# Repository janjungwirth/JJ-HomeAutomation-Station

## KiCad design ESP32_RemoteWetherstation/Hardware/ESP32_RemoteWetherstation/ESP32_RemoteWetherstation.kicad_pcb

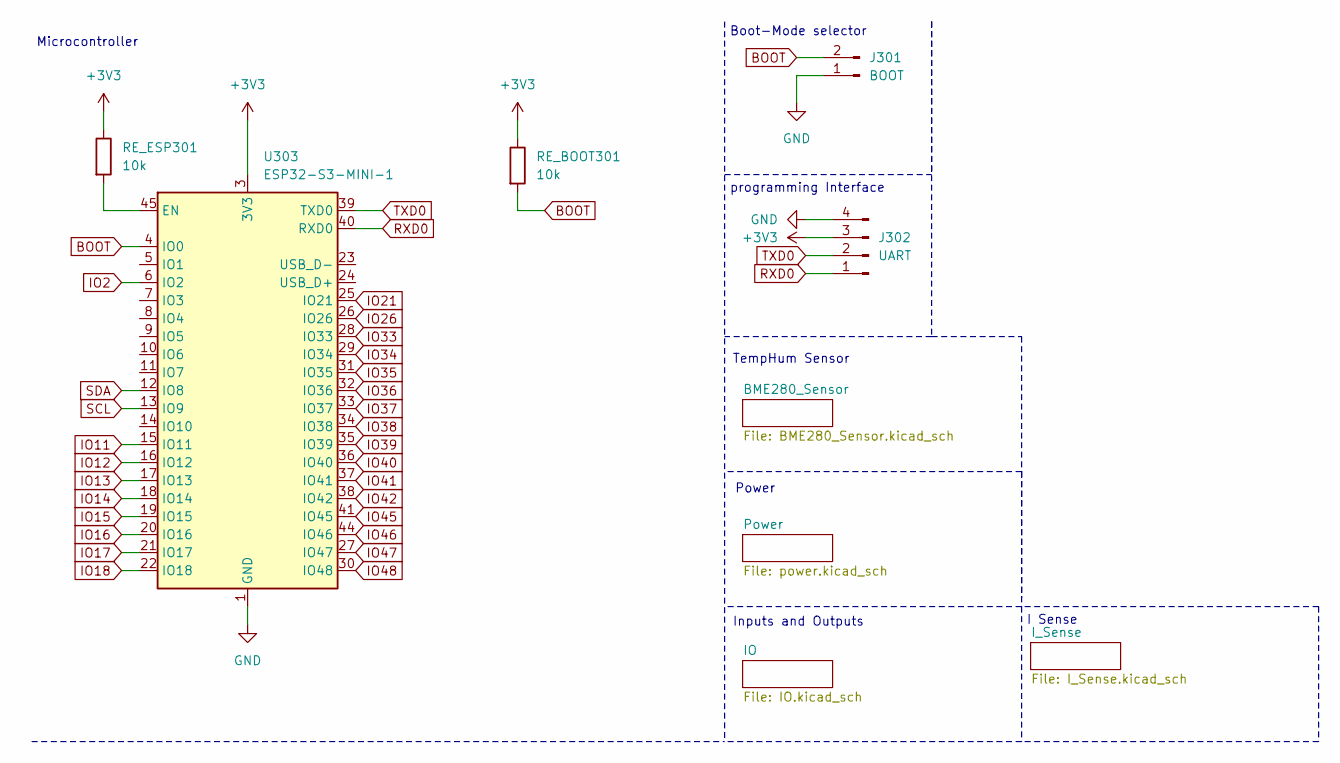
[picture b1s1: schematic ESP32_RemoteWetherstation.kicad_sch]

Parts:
J301: BOOT; PinHeader_1x02_P2.00mm_Vertical
J302: UART; PinHeader_1x04_P2.54mm_Vertical
RE_BOOT301: 10k; R_0402_1005Metric
RE_ESP301: 10k; R_0402_1005Metric
U303: ESP32-S3-MINI-1; ESP32-S2-MINI-1

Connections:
+3V3: J302.3, RE_BOOT301.1, RE_ESP301.1, U303.3 (3V3); also elsewhere on the board
BOOT: J301.2, RE_BOOT301.2, U303.4 (IO0)
GND: J301.1, J302.4, U303.1 (GND), U303.2 (GND), U303.42 (GND), U303.43 (GND), U303.46 (GND), U303.47 (GND), U303.48 (GND), U303.49 (GND), U303.50 (GND), U303.51 (GND), U303.52 (GND), U303.53 (GND), U303.54 (GND), U303.55 (GND), U303.56 (GND), U303.57 (GND), U303.58 (GND), U303.59 (GND), U303.60 (GND), U303.61 (GND), U303.62 (GND), U303.63 (GND), U303.64 (GND), U303.65 (GND); also elsewhere on the board
IO2: U303.6 (IO2)
IO11: U303.15 (IO11)
IO12: U303.16 (IO12); also elsewhere on the board
IO13: U303.17 (IO13); also elsewhere on the board
IO14: U303.18 (IO14); also elsewhere on the board
IO15: U303.19 (IO15)
IO16: U303.20 (IO16)
IO17: U303.21 (IO17)
IO18: U303.22 (IO18); also elsewhere on the board
IO21: U303.25 (IO21)
IO26: U303.26 (IO26)
IO33: U303.28 (IO33); also elsewhere on the board
IO34: U303.29 (IO34); also elsewhere on the board
IO35: U303.31 (IO35)
IO36: U303.32 (IO36)
IO37: U303.33 (IO37)
IO38: U303.34 (IO38)
IO39: U303.35 (IO39)
IO40: U303.36 (IO40)
IO41: U303.37 (IO41)
IO42: U303.38 (IO42)
IO45: U303.41 (IO45)
IO46: U303.44 (IO46)
IO47: U303.27 (IO47); also elsewhere on the board
IO48: U303.30 (IO48); also elsewhere on the board
unnamed: RE_ESP301.2, U303.45 (EN)
RXD0: J302.1, U303.40 (RXD0)
SCL: U303.13 (IO9); also elsewhere on the board
SDA: U303.12 (IO8); also elsewhere on the board
TXD0: J302.2, U303.39 (TXD0)

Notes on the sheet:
Power
Inputs and Outputs
programming Interface
I Sense
Microcontroller
Boot-Mode selector
TempHum Sensor

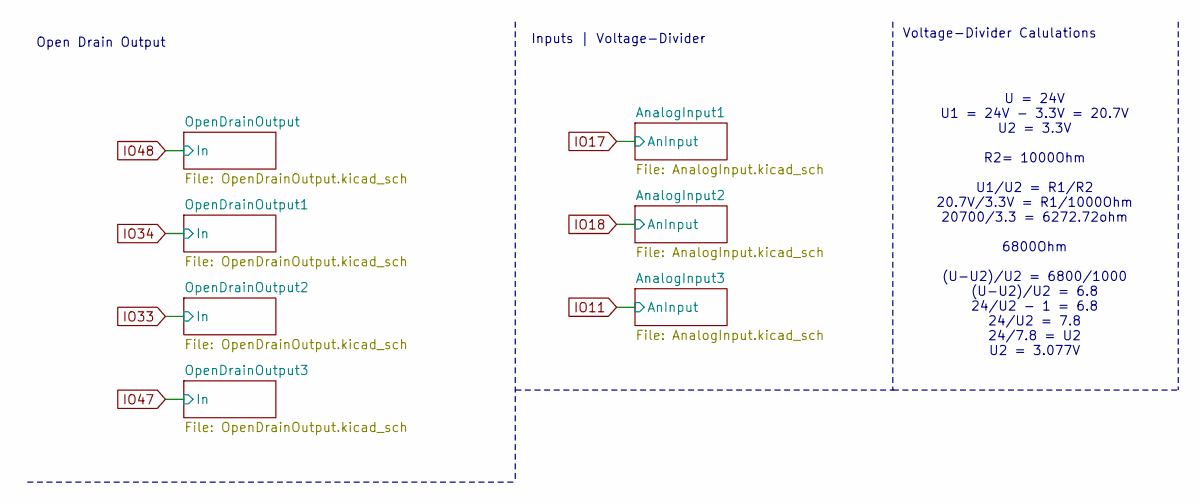
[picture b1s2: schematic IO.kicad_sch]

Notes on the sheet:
Voltage-Divider Calulations
Open Drain Output
U = 24V U1 = 24V - 3.3V = 20.7V U2 = 3.3V R2= 1000Ohm U1/U2 = R1/R2 20.7V/3.3V = R1/1000Ohm 20700/3.3 = 6272.72ohm 6800Ohm (U-U2)/U2 = 6800/1000 (U-U2)/U2 = 6.8 24/U2 - 1 = 6.8 24/U2 = 7.8 24/7.8 = U2 U2 = 3.077V
Inputs | Voltage-Divider

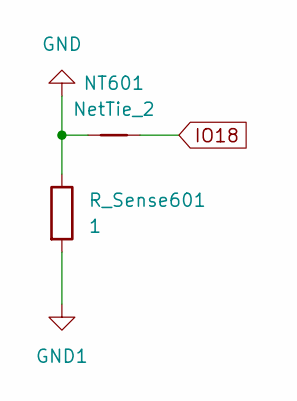
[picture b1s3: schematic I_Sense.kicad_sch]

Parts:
NT601: NetTie_2; NetTie-2_SMD_Pad0.5mm
R_Sense601: 1; R_0805_2012Metric

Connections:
GND: NT601.1, R_Sense601.1; also elsewhere on the board
GND1: R_Sense601.2; also elsewhere on the board
IO18: NT601.2; also elsewhere on the board

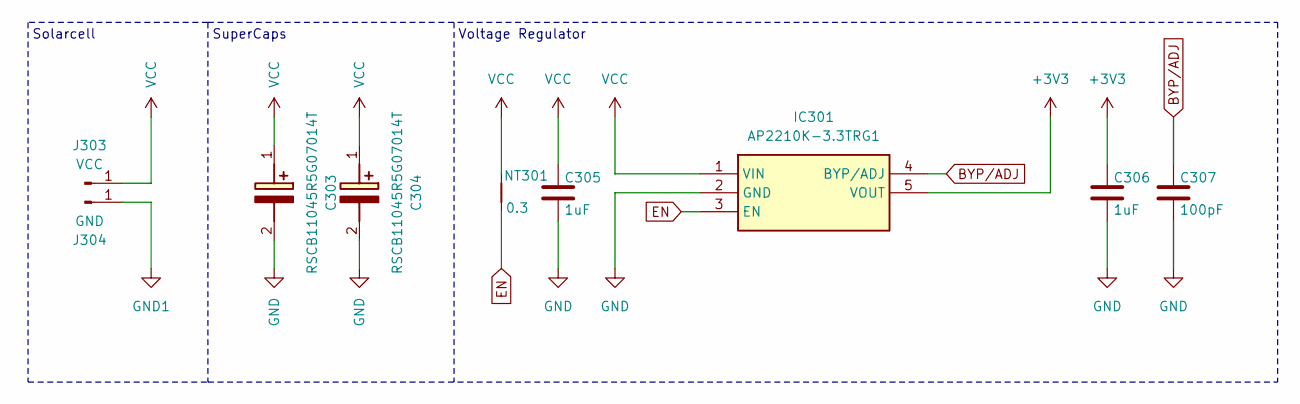
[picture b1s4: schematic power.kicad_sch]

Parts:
C303, C304: RSCB11045R5G07014T; Manufacturer_Part_Number RSCB11045R5G07014T
C305, C306: 1uF; C_0805_2012Metric_Pad1.18x1.45mm_HandSolder
C307: 100pF; C_0402_1005Metric
IC301: AP2210K-3.3TRG1; SOT95P282X145-5N; Mouser Part Number 621-AP2210K-3.3TRG1
J303: VCC; SolderWire-0.75sqmm_1x01_D1.25mm_OD2.3mm
J304: GND; SolderWire-0.75sqmm_1x01_D1.25mm_OD2.3mm
NT301: 0.3; NetTie-2_SMD_Pad0.3mm

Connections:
+3V3: C306.1, IC301.5 (VOUT); also elsewhere on the board
BYP/ADJ: C307.1, IC301.4 (BYP/ADJ)
EN: IC301.3 (EN), NT301.1
GND: C303.2 (-), C304.2 (-), C305.2, C306.2, C307.2, IC301.2 (GND); also elsewhere on the board
GND1: J304.1; also elsewhere on the board
VCC: C303.1 (+), C304.1 (+), C305.1, IC301.1 (VIN), J303.1, NT301.2

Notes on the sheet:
SuperCaps
Voltage Regulator
Solarcell

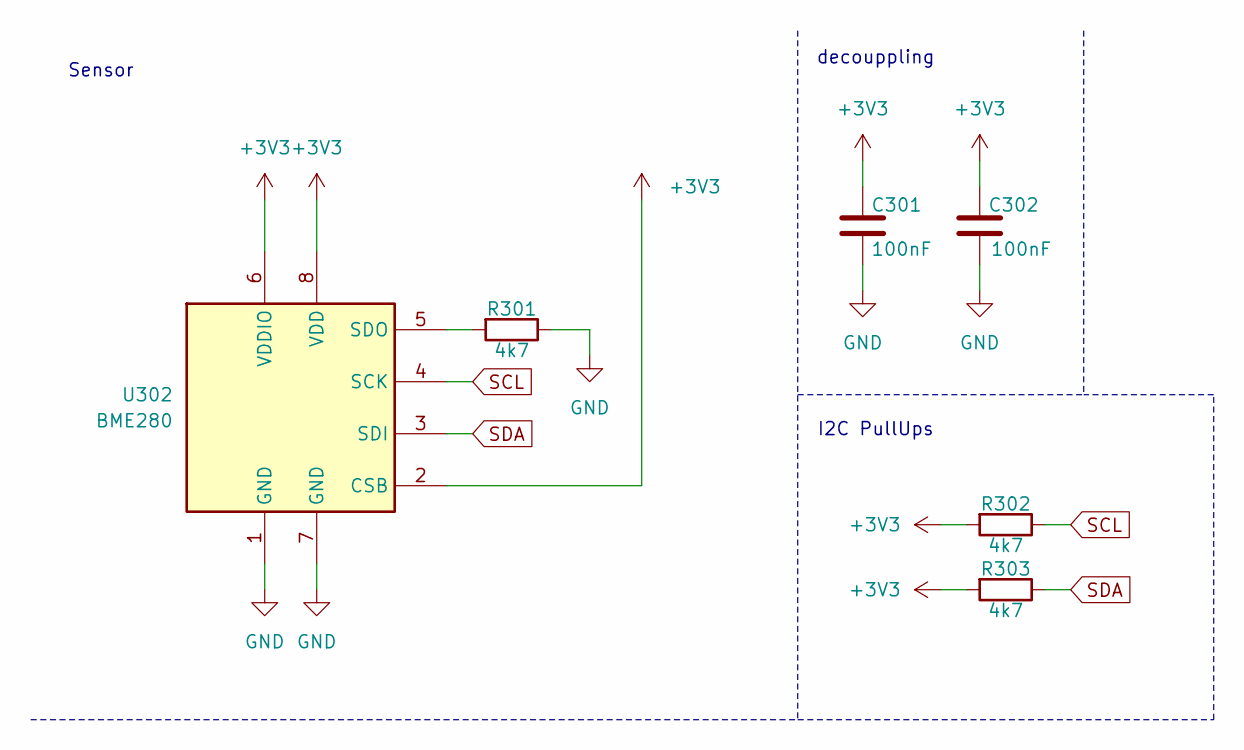
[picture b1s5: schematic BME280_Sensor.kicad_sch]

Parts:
C301, C302: 100nF; C_0402_1005Metric
R301, R302, R303: 4k7; R_0402_1005Metric
U302: BME280; Bosch_LGA-8_2.5x2.5mm_P0.65mm_ClockwisePinNumbering

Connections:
+3V3: C301.1, C302.1, R302.2, R303.2, U302.2 (CSB), U302.6 (VDDIO), U302.8 (VDD); also elsewhere on the board
GND: C301.2, C302.2, R301.1, U302.1 (GND), U302.7 (GND); also elsewhere on the board
unnamed: R301.2, U302.5 (SDO)
SCL: R302.1, U302.4 (SCK); also elsewhere on the board
SDA: R303.1, U302.3 (SDI); also elsewhere on the board

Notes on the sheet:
I2C PullUps
Sensor
decouppling

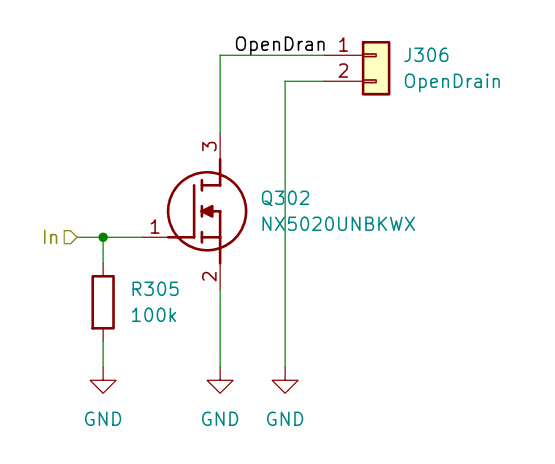
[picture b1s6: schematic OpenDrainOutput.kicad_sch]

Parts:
J306: OpenDrain; PinHeader_1x02_P2.54mm_Vertical
Q302: NX5020UNBKWX; SOT65P210X110-3N; Manufacturer_Part_Number NX5020UNBKWX
R305: 100k; R_0603_1608Metric

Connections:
/IO/OpenDrainOutput1/OpenDran: J306.1, Q302.3 (D)
GND: J306.2, Q302.2 (S), R305.2; also elsewhere on the board
IO34: Q302.1 (G), R305.1; also elsewhere on the board

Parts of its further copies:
J305, J307, J308: OpenDrain; PinHeader_1x02_P2.54mm_Vertical
Q301, Q303, Q304: NX5020UNBKWX; SOT65P210X110-3N; Manufacturer_Part_Number NX5020UNBKWX
R304, R306, R307: 100k; R_0603_1608Metric

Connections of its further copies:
/IO/OpenDrainOutput2/OpenDran: J307.1, Q303.3 (D)
/IO/OpenDrainOutput3/OpenDran: J308.1, Q304.3 (D)
/IO/OpenDrainOutput/OpenDran: J305.1, Q301.3 (D)
GND: J305.2, J307.2, J308.2, Q301.2 (S), Q303.2 (S), Q304.2 (S), R304.2, R306.2, R307.2; also elsewhere on the board
IO33: Q303.1 (G), R306.1; also elsewhere on the board
IO47: Q304.1 (G), R307.1; also elsewhere on the board
IO48: Q301.1 (G), R304.1; also elsewhere on the board

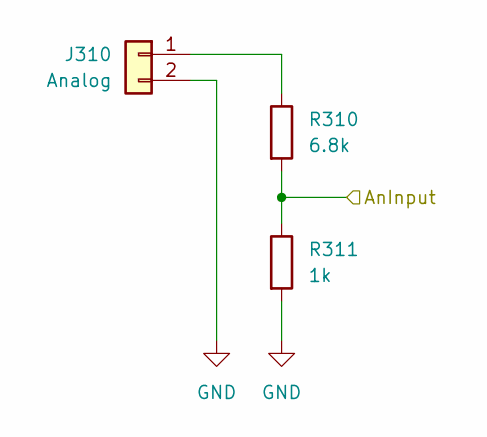
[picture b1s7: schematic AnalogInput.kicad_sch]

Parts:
J310: Analog; PinHeader_1x02_P2.54mm_Vertical
R310: 6.8k; R_0603_1608Metric
R311: 1k; R_0603_1608Metric

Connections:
GND: J310.2, R311.2; also elsewhere on the board
IO14: R310.2, R311.1; also elsewhere on the board
unnamed: J310.1, R310.1

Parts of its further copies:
J311, J312: Analog; PinHeader_1x02_P2.54mm_Vertical
R312, R314: 6.8k; R_0603_1608Metric
R313, R315: 1k; R_0603_1608Metric

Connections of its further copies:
GND: J311.2, J312.2, R313.2, R315.2; also elsewhere on the board
IO12: R312.2, R313.1; also elsewhere on the board
IO13: R314.2, R315.1; also elsewhere on the board
unnamed: J311.1, R312.1
unnamed: J312.1, R314.1

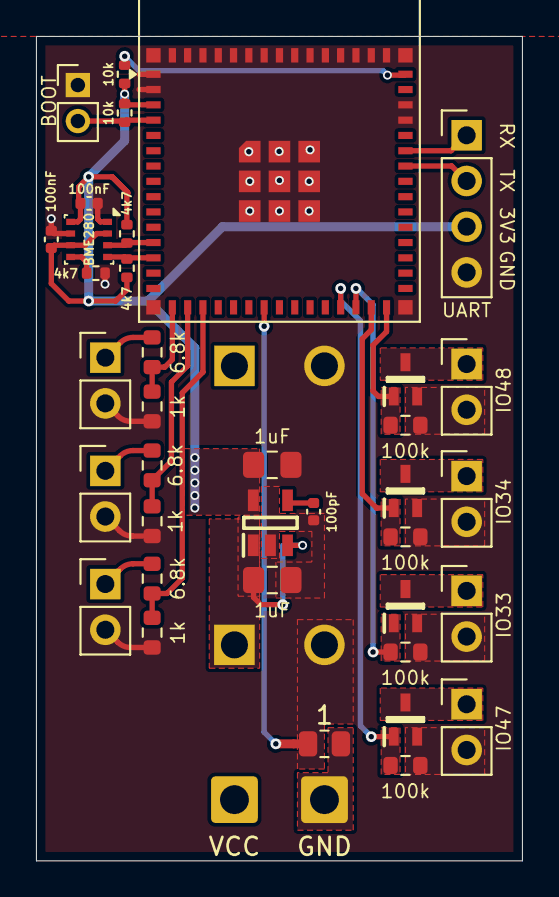
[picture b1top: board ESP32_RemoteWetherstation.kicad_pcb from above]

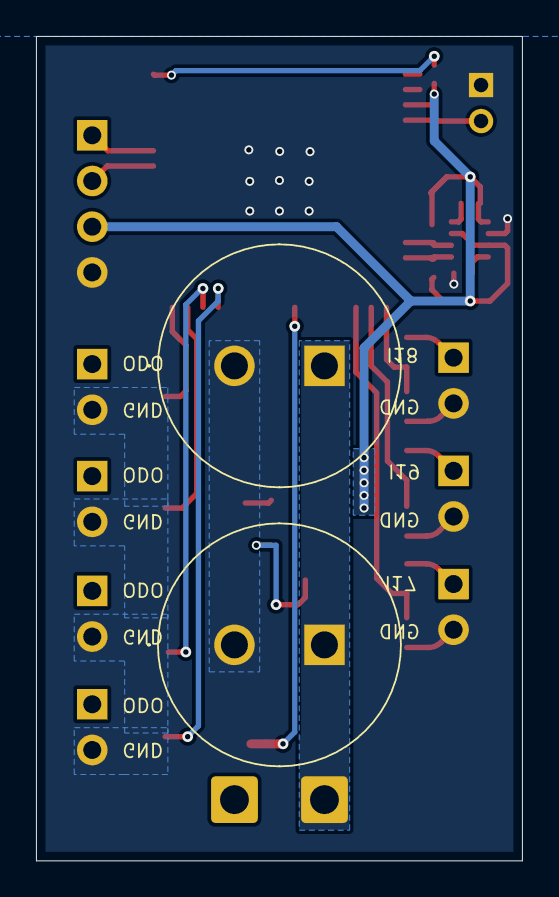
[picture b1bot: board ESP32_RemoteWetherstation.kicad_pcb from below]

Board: 2 copper layers, 27.0 x 45.8 mm, 43 parts (3 on the bottom side), 28 nets.

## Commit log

2025-11-03 test: gitpush
2025-11-03 test: gitpush (#1)
2026-02-13 feat: pcb v1
2026-02-13 Test/gitpush (#2)
    * test: gitpush
    * feat: pcb v1
2026-02-26 added IO, changed LDO
2026-02-26 added Inputs
2026-02-26 fixed merge conflicts
2026-02-26 added io (#3)
    * test: gitpush
    * feat: pcb v1
    * added IO, changed LDO
    * added Inputs
    * fixed merge conflicts
    ---------
2026-02-26 edited schematic looks
2026-02-26 Feat/change schematic looks (#4)
    * edited schematic looks
2026-02-26 deleted Backups
2026-03-02 changed MCU
2026-03-02 Change/esp32 (#5)
    * test: gitpush
    * edited schematic looks
    * deleted Backups
    * changed MCU
2026-03-02 stitching/CurrentVersion
2026-03-02 Stitching/pcb (#6)
    * test: gitpush
    * edited schematic looks
    * deleted Backups
    * stitching/CurrentVersion
2026-03-02 StitchingPCB/try1
2026-03-03 Stitching/power module (#7)
    * test: gitpush
    * edited schematic looks
    * deleted Backups
    * StitchingPCB/try1
2026-03-03 stitching/PowerModule
2026-03-16 Tested Branch Fix
2026-03-16 Test branch fix
2026-03-16 Test/branchfix (#8)
    * test: gitpush
    * edited schematic looks
    * deleted Backups
    * Tested Branch Fix
    * Test branch fix
2026-03-16 Push/commits (#9)
    * test: gitpush
    * edited schematic looks
    * deleted Backups
2026-03-16 approximately arranged components
2026-03-16 approximately arranged components (#10)
2026-04-02 placed all comps onesided
2026-04-02 placed all comps onesided (#11)
2026-04-02 Connected IO
2026-04-02 chor: error correction after DRC
2026-04-02 Pcb/bearbeiten (#12)
    * Connected IO
    * chor: error correction after DRC
